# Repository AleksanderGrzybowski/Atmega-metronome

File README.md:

This is ATmega8 based metronome, useful for my guitar practice. I needed something with wider range of BPM-s, cause my other device only goes down to 40 BPM. Sound is produced from typical 8 Ohm speaker. Board was produced in Merkar (Katowice).

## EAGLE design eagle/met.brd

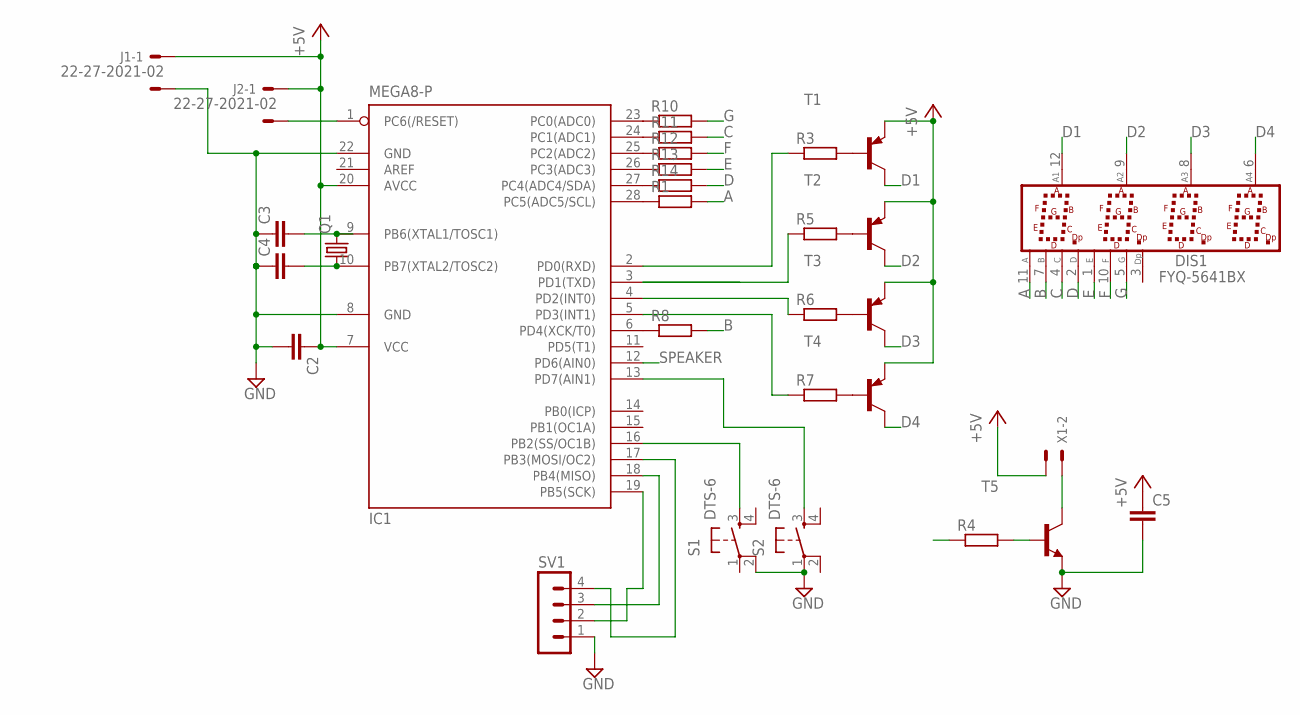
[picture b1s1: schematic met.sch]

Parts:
C2, C3, C4: C-EU025-024X044; C025-024X044
C5: C-EU075-032X103; C075-032X103
DIS1: FYQ-5641BX; FYQ5641
IC1: MEGA8-P; DIL28-3
J1, J2: 22-27-2021-02; 6410-02
Q1: CRYSTALS-NOGND-HC49; HC49
R1, R8, R10, R11, R12, R13, R14: R-EU_0204/5; 0204/5
R3, R5, R6, R7: R-EU_0207/10; 0207/10
R4: R-EU_0309/12; 0309/12
S1, S2: DTS-6
SV1: MA04-1
T1, T2, T3, T4: BC327-PNP-TO92-EBC; TO92-EBC
T5: BC337-40-NPN-TO92-CBE; TO92-CBE
X1: 22-23-2021

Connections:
+5V: C2.1, C5.1, IC1.7 (VCC), IC1.20 (AVCC), J1.1, T1.E, T2.E, T3.E, T4.E, X1.1
A: DIS1.11 (A), R1.2
B: DIS1.7 (B), R8.2
C: DIS1.4 (C), R11.2
D: DIS1.2 (D), R14.2
D1: DIS1.12 (A1), T1.C
D2: DIS1.9 (A2), T2.C
D3: DIS1.8 (A3), T3.C
D4: DIS1.6 (A4), T4.C
E: DIS1.1 (E), R13.2
F: DIS1.10 (F), R12.2
G: DIS1.5 (G), R10.2
GND: C2.2, C3.1, C4.1, C5.2, IC1.8 (GND), IC1.22 (GND), J1.2, S1.2, S2.1, SV1.1, T5.E
unnamed: C3.2, IC1.9 (PB6(XTAL1/TOSC1)), Q1.2
unnamed: C4.2, IC1.10 (PB7(XTAL2/TOSC2)), Q1.1
unnamed: R3.2, T1.B
unnamed: IC1.1 (PC6(/RESET)), J2.2
unnamed: R5.2, T2.B
unnamed: R6.2, T3.B
unnamed: R7.2, T4.B
unnamed: IC1.2 (PD0(RXD)), R3.1
unnamed: IC1.3 (PD1(TXD)), R5.1
unnamed: IC1.4 (PD2(INT0)), R6.1
unnamed: IC1.5 (PD3(INT1)), R7.1
unnamed: IC1.16 (PB2(SS/OC1B)), S1.3
unnamed: IC1.13 (PD7(AIN1)), S2.3
unnamed: IC1.6 (PD4(XCK/T0)), R8.1
unnamed: IC1.23 (PC0(ADC0)), R10.1
unnamed: IC1.24 (PC1(ADC1)), R11.1
unnamed: IC1.25 (PC2(ADC2)), R12.1
unnamed: IC1.26 (PC3(ADC3)), R13.1
unnamed: IC1.27 (PC4(ADC4/SDA)), R14.1
unnamed: IC1.28 (PC5(ADC5/SCL)), R1.1
unnamed: T5.C, X1.2
unnamed: IC1.19 (PB5(SCK)), SV1.2
unnamed: IC1.18 (PB4(MISO)), SV1.3
unnamed: IC1.17 (PB3(MOSI/OC2)), SV1.4
OFDS: R4.2, T5.B
SPEAKER: IC1.12 (PD6(AIN0)), R4.1

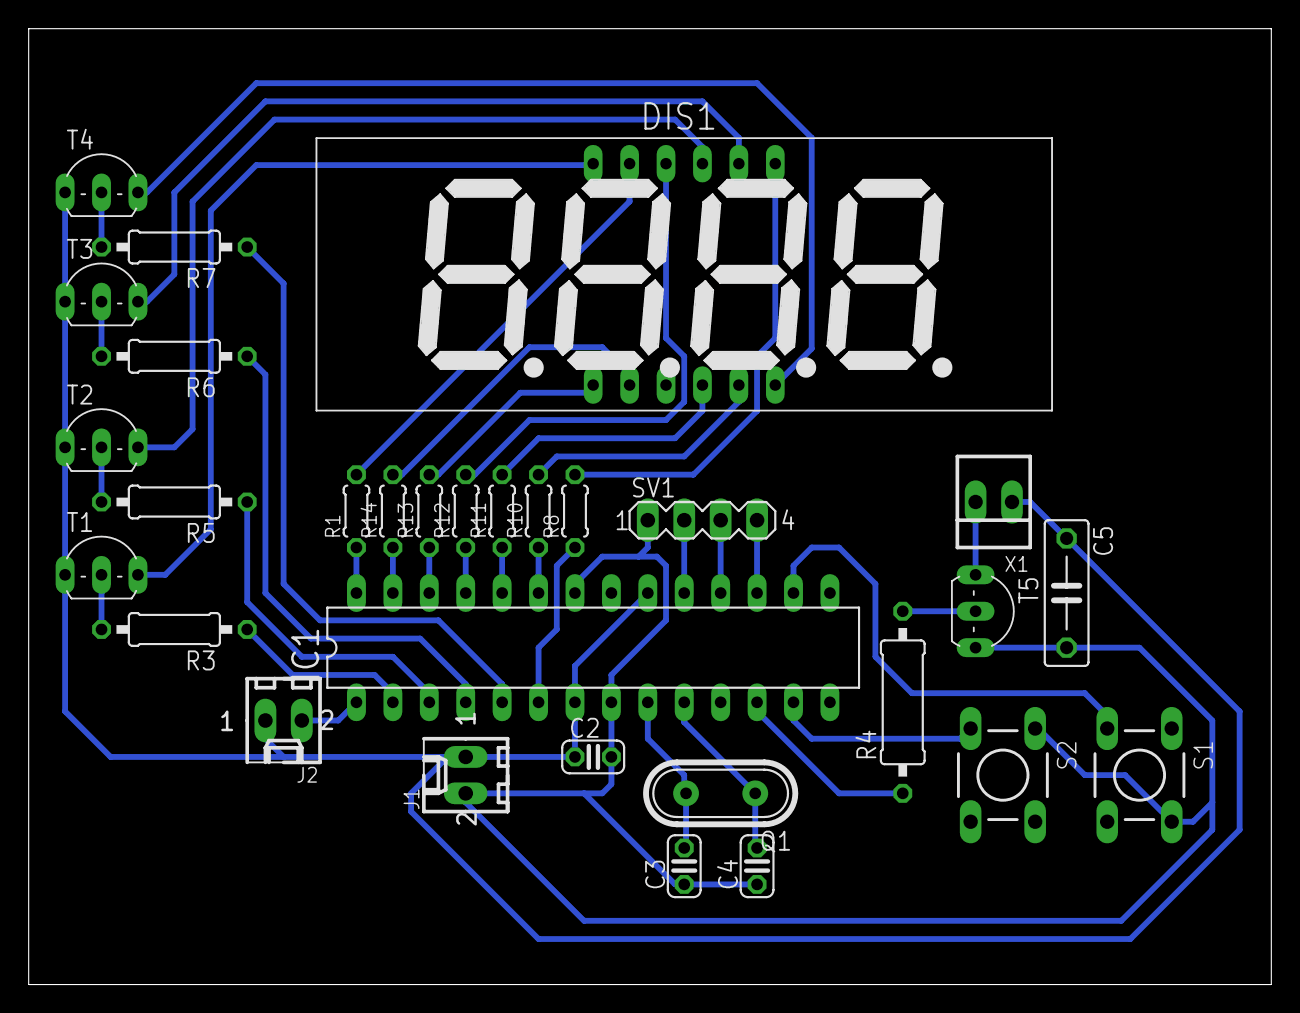
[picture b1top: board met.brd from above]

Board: 2 copper layers, 86.7 x 66.7 mm, 30 parts (0 on the bottom side), 39 nets.

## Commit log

2016-08-18 Hardware setup, base project
2016-08-18 Working TIMER1
2016-08-18 Working both timers
2016-08-18 Working display
2016-08-18 Working showing bpm
2016-08-18 Working buttons
2016-08-18 Rhythm animation, separate file for bpm data, cleanup
2016-08-18 Cleanup, remove ghosting 'fix'
2016-09-08 Shuffle IO around to match the board
2016-09-08 No idea
2016-09-08 Fix refactoring error, faster rolling
2016-09-08 Eagle schematic and board
2016-09-15 Photo
2016-09-15 Cleanup
2016-09-16 Readme
